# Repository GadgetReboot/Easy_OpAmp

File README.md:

# Easy_OpAmp
Breadboard friendly op amp break out board module with on board negative supply generator

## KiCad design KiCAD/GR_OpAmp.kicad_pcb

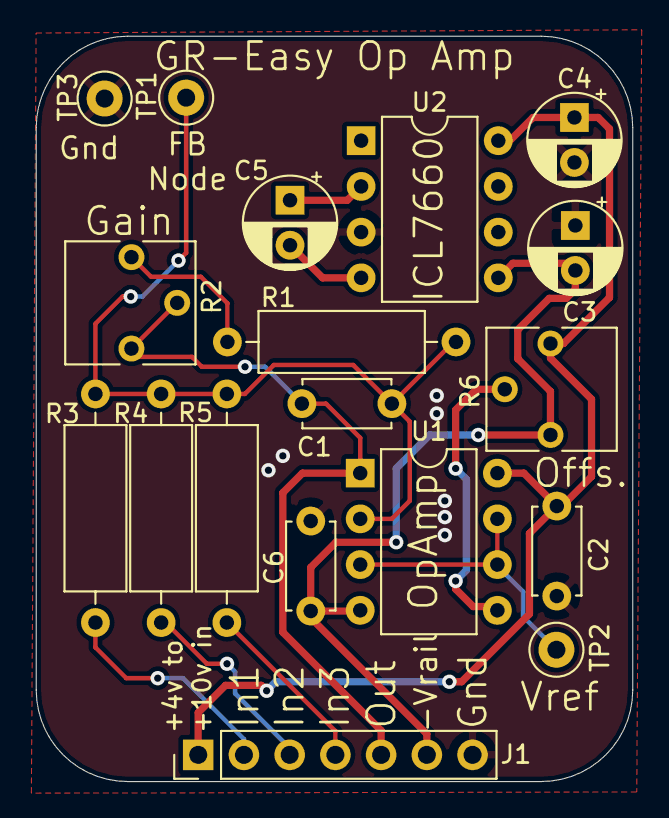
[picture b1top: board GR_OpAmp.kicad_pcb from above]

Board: 2 copper layers, 33.1 x 41.4 mm, 18 parts (0 on the bottom side), 13 nets.

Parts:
C1: DNI; C_Disc_D4.7mm_W2.5mm_P5.00mm
C2, C6: 100nF; C_Disc_D4.7mm_W2.5mm_P5.00mm
C3, C4, C5: 10uF; CP_Radial_D5.0mm_P2.50mm
J1: Conn_01x07; PinHeader_1x07_P2.54mm_Vertical
R1: 4K7; R_Axial_DIN0309_L9.0mm_D3.2mm_P12.70mm_Horizontal
R2, R6: 100K; Potentiometer_Vishay_T73YP_Vertical
R3, R4, R5: 10K; R_Axial_DIN0309_L9.0mm_D3.2mm_P12.70mm_Horizontal
TP1, TP2, TP3: TestPoint; TestPoint_Loop_D1.80mm_Drill1.0mm_Beaded
U1: LM358; DIP-8_W7.62mm
U2: ICL7660; DIP-8_W7.62mm

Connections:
/In1: J1.2, R3.2
/In2: J1.3, R4.2
/In3: J1.4, R5.2
/Out: C1.1, J1.5, R2.1, R2.2, U1.1
/Vref: TP2.1, U1.3, U1.6, U1.7
GNDREF: C2.1, C3.1, C4.2, C6.1, J1.7, TP3.1, U2.3
unnamed: C1.2, R1.2, R3.1, R4.1, R5.1, TP1.1, U1.2
unnamed: C5.1, U2.2
unnamed: C5.2, U2.4
unnamed: R1.1, R2.3
unnamed: R6.2, U1.5
VCC: C2.2, C4.1, J1.1, R6.1, U1.8, U2.8
VSS: C3.2, C6.2, J1.6, R6.3, U1.4, U2.5
